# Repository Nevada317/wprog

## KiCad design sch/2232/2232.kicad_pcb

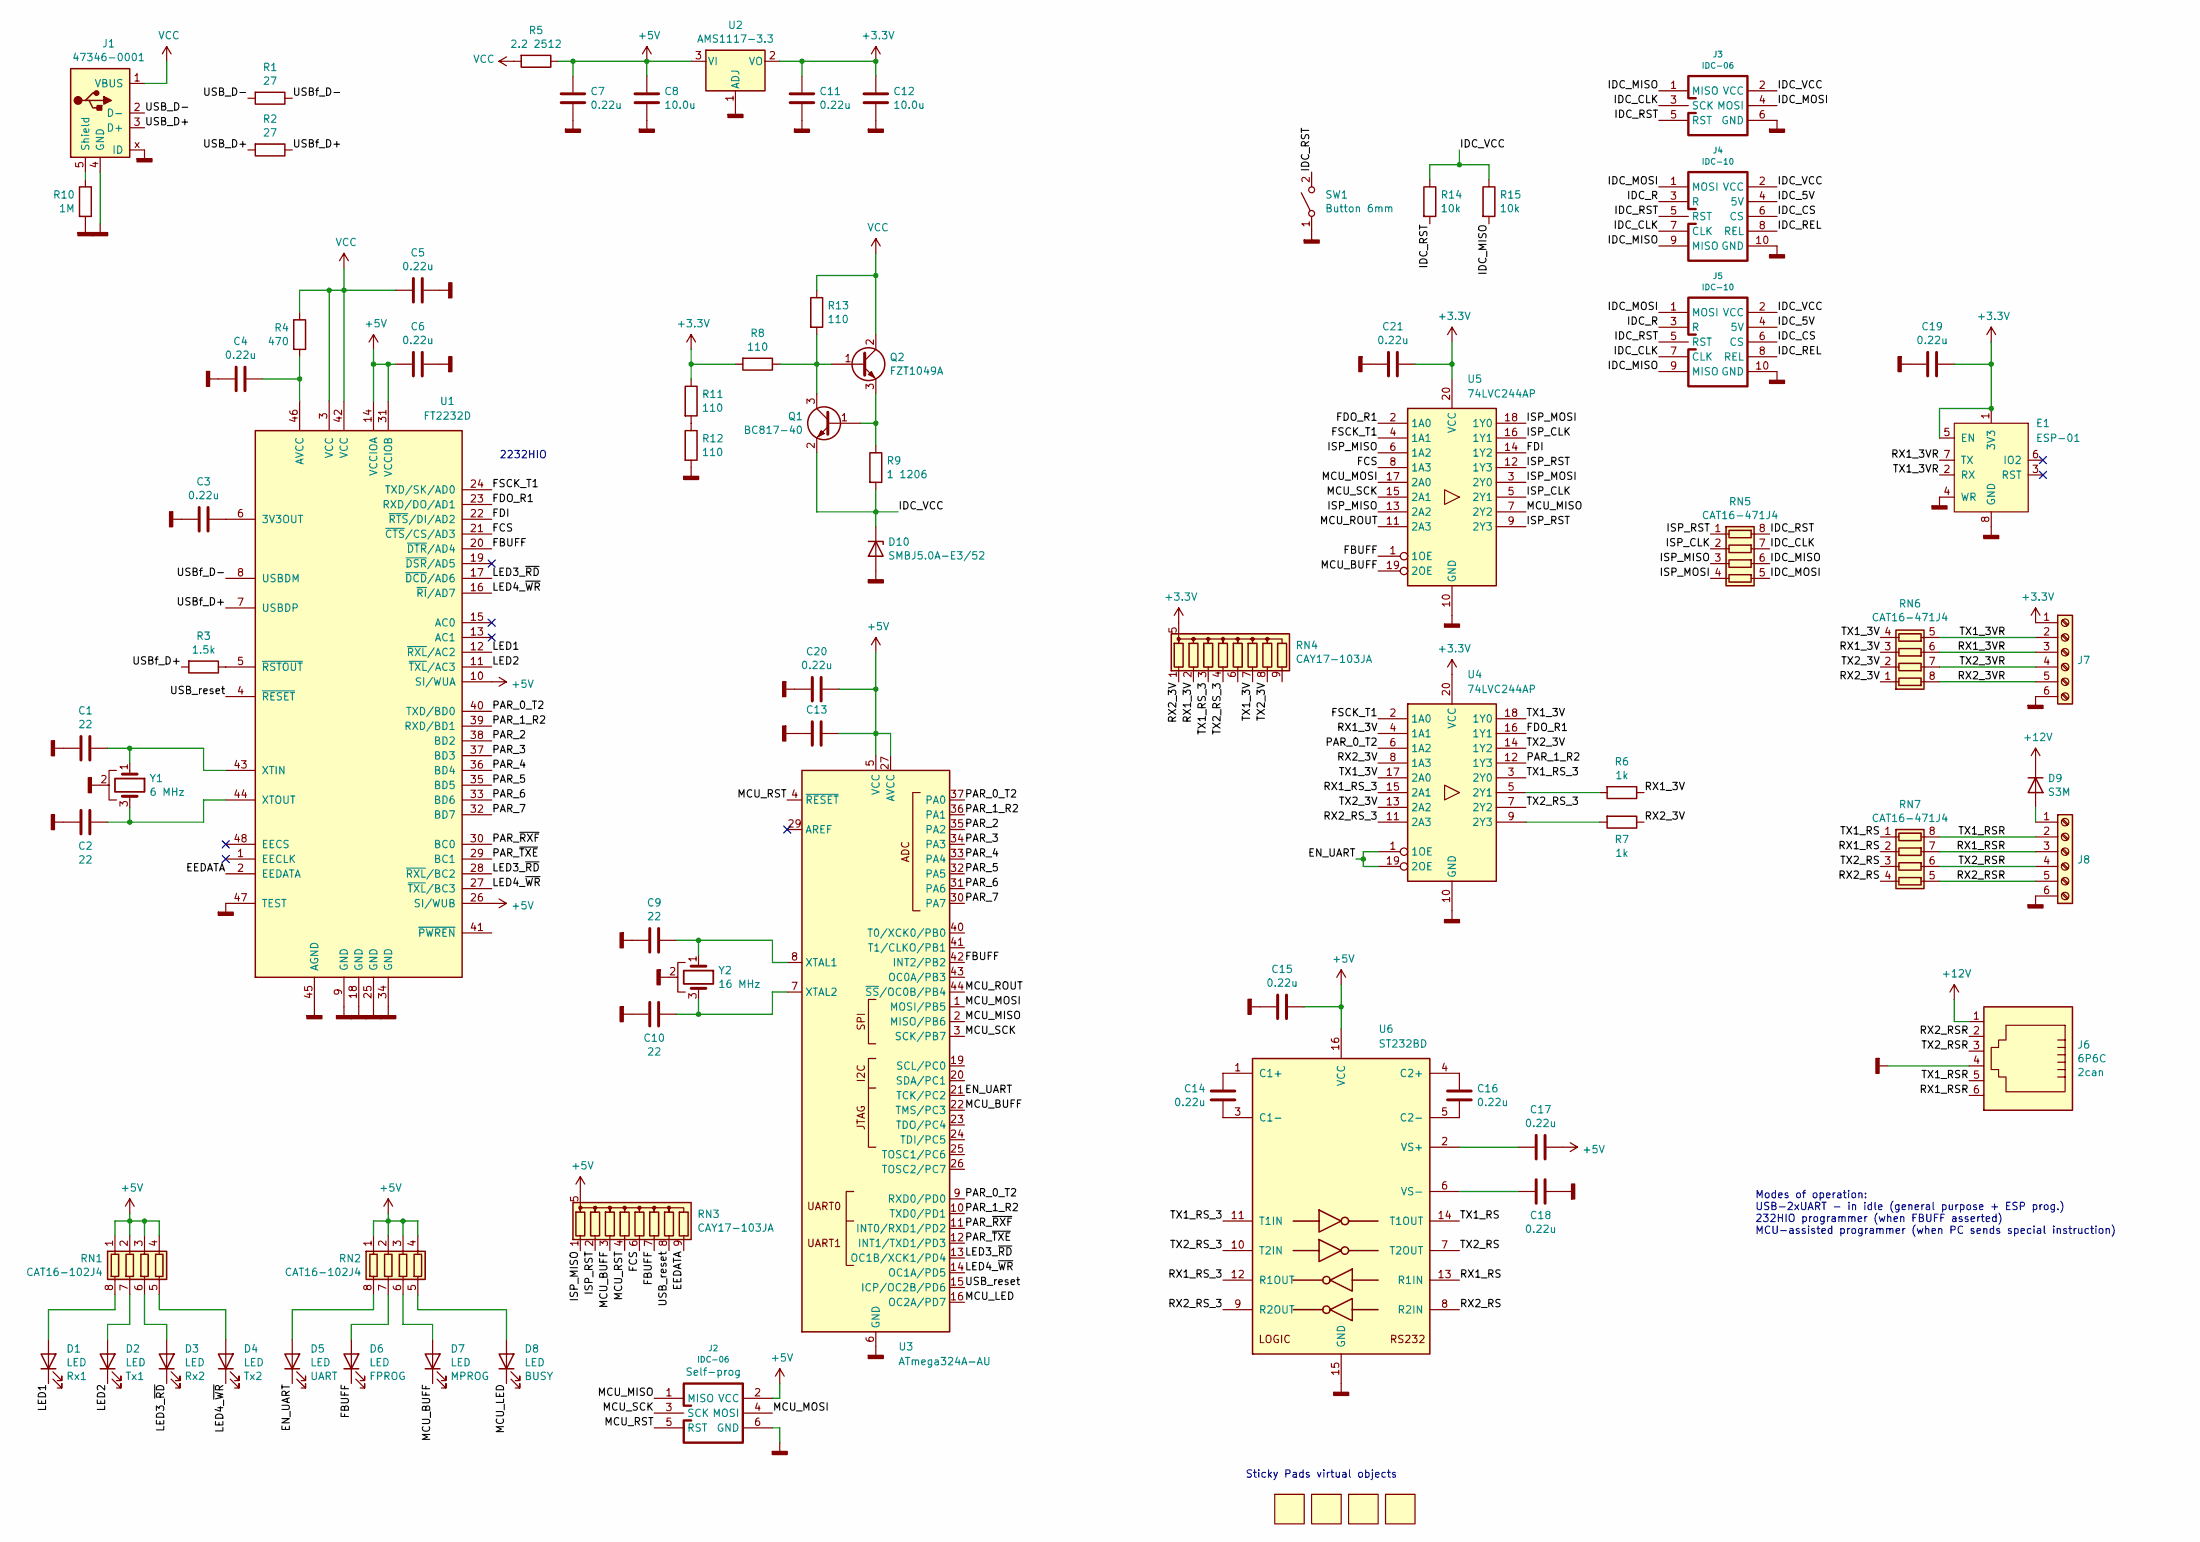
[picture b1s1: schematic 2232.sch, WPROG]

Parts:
C1, C2, C9, C10: 22; C_0603
C3, C4, C5, C6, C7, C11, C13, C14, C15, C16, C17, C18, C19, C20, C21: 0.22u; C_0603
C8, C12: 10.0u; C_1206
D1, D2, D3, D4, D5, D6, D7, D8: LED; LED_KP-2012G
D9: S3M; DO-214AB_SMC
D10: SMBJ5.0A-E3/52; DO-214AA_SMB
E1: ESP-01
J1: 47346-0001; USB_micro_47346
J2: IDC-06; PLD-6
J3: IDC-06; IDC_Header_Straight_6pins
J4, J5: IDC-10; IDC_Header_Straight_10pins
J6: 6P6C; TJ1A-6P6C_new
J7, J8: Screw_Terminal_01x06; Terminal_3.5mm_x6
Q1: BC817-40; SOT-23
Q2: FZT1049A; SOT-223
R1, R2: 27; R_0603
R3: 1.5k; R_0603
R4: 470; R_0603
R5: 2.2 2512; R_2512
R6, R7: 1k; R_0603
R8, R11, R12, R13: 110; R_0603
R9: 1 1206; R_1206
R10: 1M; R_0603
R14, R15: 10k; R_0603
RN1, RN2: CAT16-102J4; R_CAT-16-4
RN3, RN4: CAY17-103JA; R_CAY17
RN5, RN6, RN7: CAT16-471J4; R_CAT-16-4
SW1: Button 6mm; SW_PUSH_6mm
U1: FT2232D; LQFP-48_7x7mm_P0.5mm
U2: AMS1117-3.3; SOT-223
U3: ATmega324A-AU; TQFP-44
U4, U5: 74LVC244AP; TSSOP-20
U6: ST232BD; SOIC-16
V1, V2, V3, V4: Virtual; StickyPad_13mm
Y1: 6 MHz; Crystal_HC-49SMD
Y2: 16 MHz; Crystal_HC-49SMD

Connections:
+3V3: C11.1, C12.1, C19.1, C21.1, E1.1 (3V3), E1.5 (EN), J7.1, R8.2, R11.1, RN4.5 (common), RN4.10 (common), U2.2 (VO), U4.20 (VCC), U5.20 (VCC)
+5V: C6.1, C7.1, C8.1, C13.1, C15.2, C17.1, C20.1, J2.2 (VCC), R5.1, RN1.1 (R1.1), RN1.2 (R2.1), RN1.3 (R3.1), RN1.4 (R4.1), RN2.1 (R1.1), RN2.2 (R2.1), RN2.3 (R3.1), RN2.4 (R4.1), RN3.5 (common), RN3.10 (common), U1.10 (SI/WUA), U1.14 (VCCIOA), U1.26 (SI/WUB), U1.31 (VCCIOB), U2.3 (VI), U3.5 (VCC), U3.17 (VCC), U3.27 (AVCC), U3.38 (VCC), U6.16 (VCC)
+12V: D9.1 (K), J6.1
/EEDATA: RN3.9 (R8), U1.2 (EEDATA)
/EN_UART: D5.1 (K), U3.21 (TCK/PC2), U4.1 (1OE), U4.19 (2OE)
/FBUFF: D6.1 (K), RN3.7 (R6), U1.20 (~DTR~/AD4), U3.42 (INT2/PB2), U5.1 (1OE)
/FCS: RN3.6 (R5), U1.21 (~CTS~/CS/AD3), U5.8 (1A3)
/FDI: U1.22 (~RTS~/DI/AD2), U5.14 (1Y2)
/FDO_R1: U1.23 (RXD/DO/AD1), U4.16 (1Y1), U5.2 (1A0)
/FSCK_T1: U1.24 (TXD/SK/AD0), U4.2 (1A0), U5.4 (1A1)
/IDC_5V: J4.4 (5V), J5.4 (5V)
/IDC_CLK: J3.3 (SCK), J4.7 (CLK), J5.7 (CLK), RN5.7 (R2.2)
/IDC_CS: J4.6 (CS), J5.6 (CS)
/IDC_MISO: J3.1 (MISO), J4.9 (MISO), J5.9 (MISO), R15.2, RN5.6 (R3.2)
/IDC_MOSI: J3.4 (MOSI), J4.1 (MOSI), J5.1 (MOSI), RN5.5 (R4.2)
/IDC_R: J4.3 (R), J5.3 (R)
/IDC_REL: J4.8 (REL), J5.8 (REL)
/IDC_RST: J3.5 (RST), J4.5 (RST), J5.5 (RST), R14.2, RN5.8 (R1.2), SW1.2 (B)
/IDC_VCC: D10.1 (K), J3.2 (VCC), J4.2 (VCC), J5.2 (VCC), Q1.2 (E), R9.2, R14.1, R15.1
/ISP_CLK: RN5.2 (R2.1), U5.5 (2Y1), U5.16 (1Y1)
/ISP_MISO: RN3.1 (R1), RN5.3 (R3.1), U5.6 (1A2), U5.13 (2A2)
/ISP_MOSI: RN5.4 (R4.1), U5.3 (2Y0), U5.18 (1Y0)
/ISP_RST: RN3.2 (R2), RN5.1 (R1.1), U5.9 (2Y3), U5.12 (1Y3)
/LED1: D1.1 (K), U1.12 (~RXL~/AC2)
/LED2: D2.1 (K), U1.11 (~TXL~/AC3)
/LED3_~RD: D3.1 (K), U1.17 (~DCD~/AD6), U1.28 (~RXL~/BC2), U3.13 (OC1B/XCK1/PD4)
/LED4_~WR: D4.1 (K), U1.16 (~RI~/AD7), U1.27 (~TXL~/BC3), U3.14 (OC1A/PD5)
/MCU_BUFF: D7.1 (K), RN3.3 (R3), U3.22 (TMS/PC3), U5.19 (2OE)
/MCU_LED: D8.1 (K), U3.16 (OC2A/PD7)
/MCU_MISO: J2.1 (MISO), U3.2 (MISO/PB6), U5.7 (2Y2)
/MCU_MOSI: J2.4 (MOSI), U3.1 (MOSI/PB5), U5.17 (2A0)
/MCU_ROUT: U3.44 (~SS~/OC0B/PB4), U5.11 (2A3)
/MCU_RST: J2.5 (RST), RN3.4 (R4), U3.4 (~RESET)
/MCU_SCK: J2.3 (SCK), U3.3 (SCK/PB7), U5.15 (2A1)
/PAR_0_T2: U1.40 (TXD/BD0), U3.9 (RXD0/PD0), U3.37 (PA0), U4.6 (1A2)
/PAR_1_R2: U1.39 (RXD/BD1), U3.10 (TXD0/PD1), U3.36 (PA1), U4.12 (1Y3)
/PAR_2: U1.38 (BD2), U3.35 (PA2)
/PAR_3: U1.37 (BD3), U3.34 (PA3)
/PAR_4: U1.36 (BD4), U3.33 (PA4)
/PAR_5: U1.35 (BD5), U3.32 (PA5)
/PAR_6: U1.33 (BD6), U3.31 (PA6)
/PAR_7: U1.32 (BD7), U3.30 (PA7)
/PAR_~RXF: U1.30 (BC0), U3.11 (INT0/RXD1/PD2)
/PAR_~TXE: U1.29 (BC1), U3.12 (INT1/TXD1/PD3)
/RX1_3V: R6.1, RN4.2 (R2), RN6.3 (R3.1), U4.4 (1A1)
/RX1_3VR: E1.7 (TX), J7.3, RN6.6 (R3.2)
/RX1_RS: RN7.2 (R2.1), U6.13 (R1IN)
/RX1_RSR: J6.6, J8.3, RN7.7 (R2.2)
/RX1_RS_3: U4.15 (2A1), U6.12 (R1OUT)
/RX2_3V: R7.1, RN4.1 (R1), RN6.1 (R1.1), U4.8 (1A3)
/RX2_3VR: J7.5, RN6.8 (R1.2)
/RX2_RS: RN7.4 (R4.1), U6.8 (R2IN)
/RX2_RSR: J6.2, J8.5, RN7.5 (R4.2)
/RX2_RS_3: U4.11 (2A3), U6.9 (R2OUT)
/TX1_3V: RN4.7 (R6), RN6.4 (R4.1), U4.17 (2A0), U4.18 (1Y0)
/TX1_3VR: E1.2 (RX), J7.2, RN6.5 (R4.2)
/TX1_RS: RN7.1 (R1.1), U6.14 (T1OUT)
/TX1_RSR: J6.5, J8.2, RN7.8 (R1.2)
/TX1_RS_3: RN4.3 (R3), U4.3 (2Y0), U6.11 (T1IN)
/TX2_3V: RN4.8 (R7), RN6.2 (R2.1), U4.13 (2A2), U4.14 (1Y2)
/TX2_3VR: J7.4, RN6.7 (R2.2)
/TX2_RS: RN7.3 (R3.1), U6.7 (T2OUT)
/TX2_RSR: J6.3, J8.4, RN7.6 (R3.2)
/TX2_RS_3: RN4.4 (R4), U4.7 (2Y2), U6.10 (T2IN)
/USB_D+: J1.3 (D+), R2.2
/USB_D-: J1.2 (D-), R1.2
/USB_reset: RN3.8 (R7), U1.4 (~RESET), U3.15 (ICP/OC2B/PD6)
/USBf_D+: R2.1, R3.2, U1.7 (USBDP)
/USBf_D-: R1.1, U1.8 (USBDM)
GNDD: C1.2, C2.2, C3.2, C4.2, C5.2, C6.2, C7.2, C8.2, C9.2, C10.2, C11.2, C12.2, C13.2, C15.1, C18.1, C19.2, C20.2, C21.2, D10.2 (A), E1.4 (WR), E1.8 (GND), J1.4 (GND), J1.x (ID), J2.6 (GND), J3.6 (GND), J4.10 (GND), J5.10 (GND), J6.4, J7.6, J8.6, R10.2, R12.2, SW1.1 (A), U1.9 (GND), U1.18 (GND), U1.25 (GND), U1.34 (GND), U1.45 (AGND), U1.47 (TEST), U2.1 (ADJ), U3.6 (GND), U3.18 (GND), U3.28 (GND), U3.39 (GND), U4.10 (GND), U5.10 (GND), U6.15 (GND), Y1.2, Y2.2
unnamed: C1.1, U1.43 (XTIN), Y1.1
unnamed: C2.1, U1.44 (XTOUT), Y1.3
unnamed: C3.1, U1.6 (3V3OUT)
unnamed: C4.1, R4.2, U1.46 (AVCC)
unnamed: C9.1, U3.8 (XTAL1), Y2.1
unnamed: C10.1, U3.7 (XTAL2), Y2.3
unnamed: C14.1, U6.1 (C1+)
unnamed: C14.2, U6.3 (C1-)
unnamed: C16.1, U6.4 (C2+)
unnamed: C16.2, U6.5 (C2-)
unnamed: C17.2, U6.2 (VS+)
unnamed: C18.2, U6.6 (VS-)
unnamed: D1.2 (A), RN1.8 (R1.2)
unnamed: D2.2 (A), RN1.7 (R2.2)
unnamed: D3.2 (A), RN1.6 (R3.2)
unnamed: D4.2 (A), RN1.5 (R4.2)
unnamed: D5.2 (A), RN2.8 (R1.2)
unnamed: D6.2 (A), RN2.7 (R2.2)
unnamed: D7.2 (A), RN2.6 (R3.2)
unnamed: D8.2 (A), RN2.5 (R4.2)
unnamed: D9.2 (A), J8.1
unnamed: J1.5 (Shield), R10.1
unnamed: Q1.1 (B), Q2.3 (E), R9.1
unnamed: Q1.3 (C), Q2.1 (B), R8.1, R13.2
unnamed: R3.1, U1.5 (~RSTOUT)
unnamed: R6.2, U4.5 (2Y1)
unnamed: R7.2, U4.9 (2Y3)
unnamed: R11.2, R12.1
VCC: C5.1, J1.1 (VBUS), Q2.2 (C), R4.1, R5.2, R13.1, U1.3 (VCC), U1.42 (VCC)

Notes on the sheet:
2232HIO
Modes of operation: USB-2xUART - in idle (general purpose + ESP prog.) 232HIO programmer (when FBUFF asserted) MCU-assisted programmer (when PC sends special instruction)
Sticky Pads virtual objects

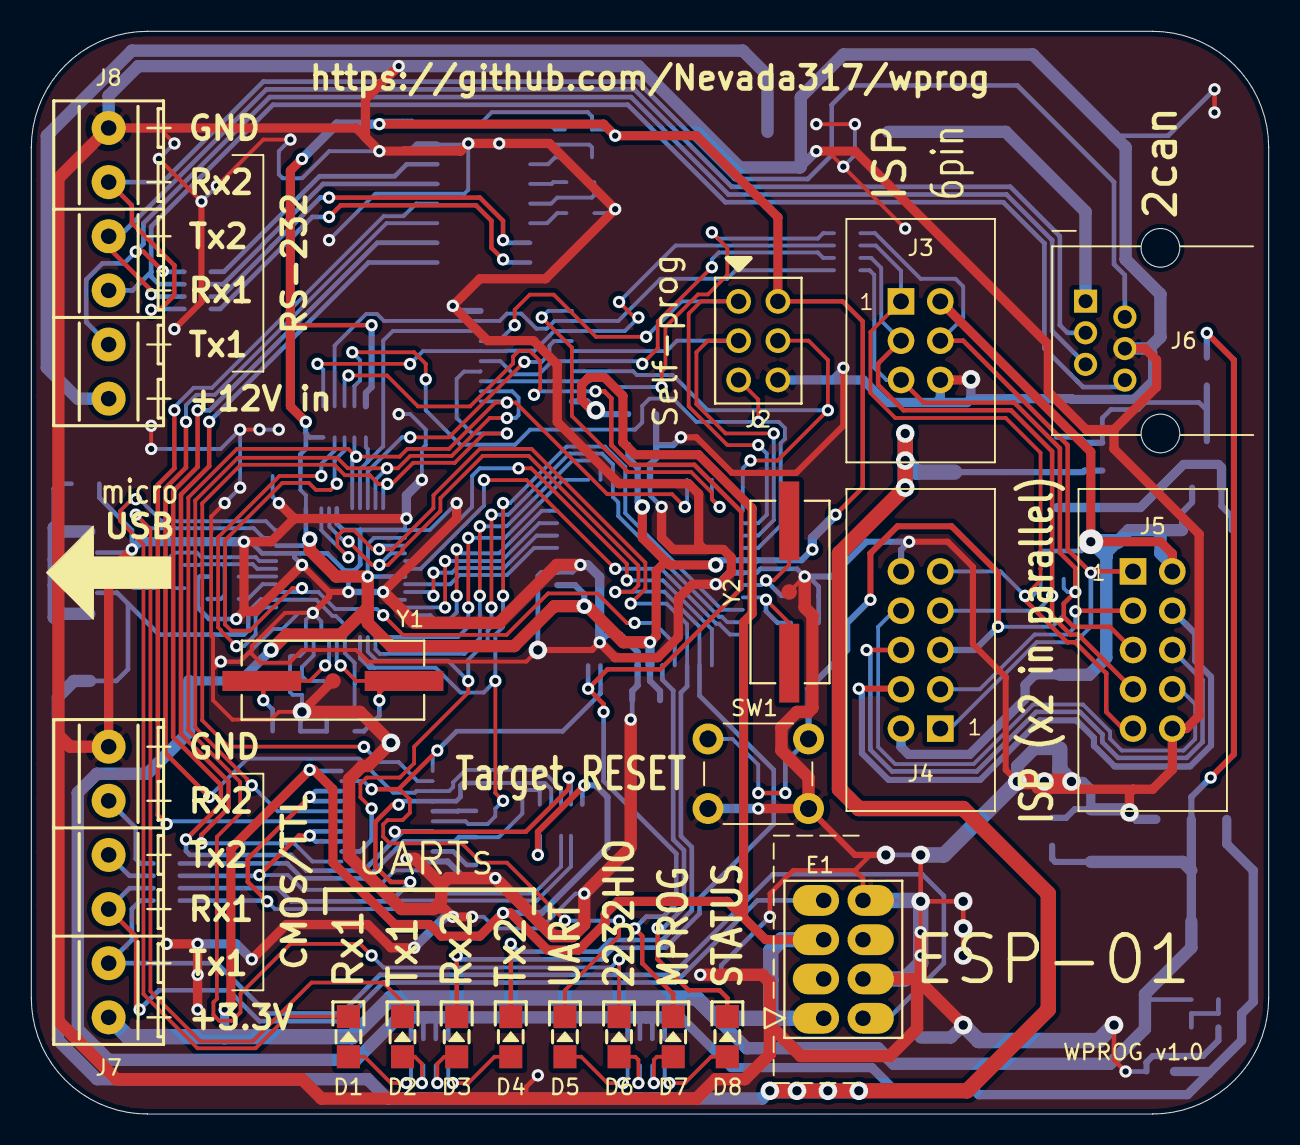
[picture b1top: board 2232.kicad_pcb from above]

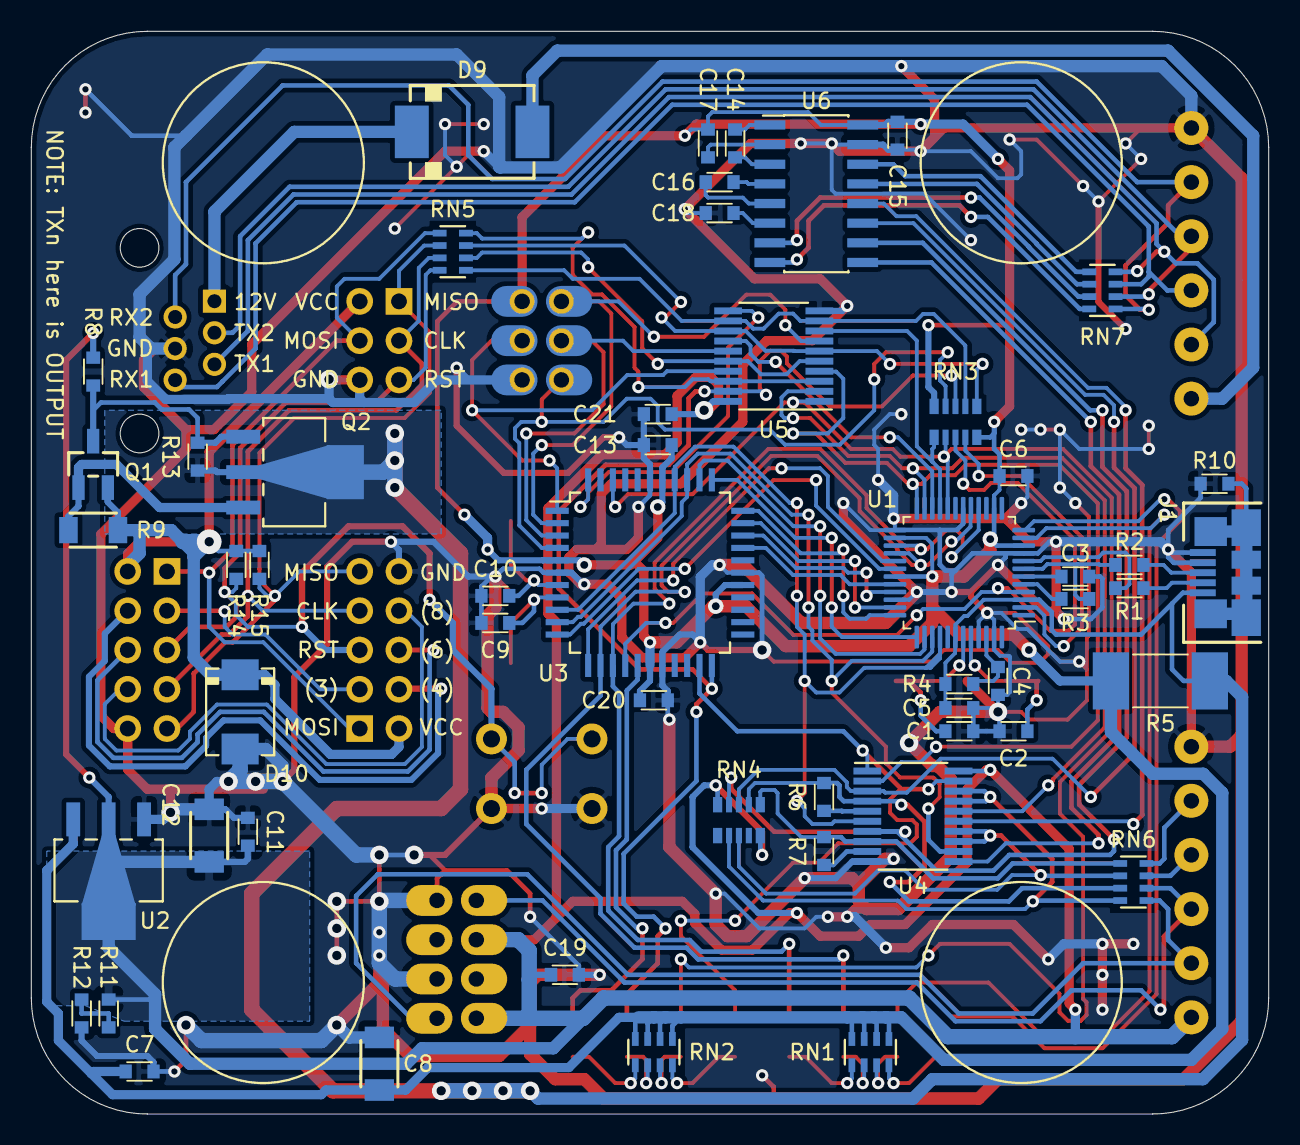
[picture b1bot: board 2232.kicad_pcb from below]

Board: 2 copper layers, 80.0 x 70.0 mm, 77 parts (58 on the bottom side), 99 nets.

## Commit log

2020-11-21 Some thoughts
2020-12-11 Schematic stub
2020-12-12 Strobes added
2020-12-12 HC138 added
2020-12-12 Names fixed. Footprints assigned
2020-12-12 Annotated. PCB exported
2020-12-12 PCB orientation stub
2020-12-12 UART multiplexing
2020-12-13 Routing started
2020-12-14 UARTs routed trough connectors
2020-12-14 All components on-board
2020-12-14 RN remap
2020-12-14 Sides separated
2020-12-14 ISP routed
2020-12-14 All footprinted elements are routed
2020-12-15 VCC routed
2020-12-15 IDC rotated
2020-12-15 Zones added
2020-12-16 Cleanup
2020-12-16 No-fill zones
2020-12-16 Minor updates
2020-12-19 pcb updates. Looks ready
2020-12-19 PCB silk added
2020-12-19 Gerbers exported
2020-12-19 STEP models update
2020-12-20 Pullups to RST and MISO added
2020-12-20 Silk updates
2020-12-20 Reset button added
2020-12-20 zipped
2020-12-20 Step update
2020-12-20 Remove duplicate PDF
2020-12-26 Include stub added
2020-12-26 Loop added
2020-12-26 Macro file added
2020-12-26 Memclear added
2020-12-26 Pin init
2020-12-26 Mode selector created
2021-01-05 UART Rx stub added
2021-01-05 PC C stub added
2021-01-05 Option parser added
2021-01-05 Add variable to store input string (port)
2021-01-05 Task.c/h added and looks like working
2021-01-05 Pages linked list implemented
2021-01-05 Pages called
2021-01-05 Tasks structure changed
2021-01-05 Intel hex parser added
2021-01-06 Data from ihex is now separated by pages
2021-01-06 tty.c inserted
2021-01-06 UART looks like working
2021-01-07 Transport constructor/destructor added
2021-01-07 Subscribers added
2021-01-07 Transport parcel - raw parcel generated and printed
2021-01-07 Byte stuffing added
2021-01-07 Data sent to real port
2021-01-07 Reader in separate thread added
2021-01-07 Data should be stored now
2021-01-07 Reader looks like working
2021-01-07 CRC added
2021-01-07 Removet bunch of useless printf's
2021-01-08 Specs update
2021-01-08 Protocol constants defined as pc/src/protocol.h
2021-01-11 Remove nasty warning in test case
2022-02-01 Update Makefile
2022-02-01 Debug calls added
2022-02-01 Init ONE register
2022-02-01 Modified echo added to 1w module
2022-02-01 Bit operations implemented
2022-02-01 Fix reset
2022-02-01 Read rom works
2023-05-05 Add m164p support
2023-05-05 ISR table separation
2023-05-05 Remove gefault MEGA and fix dependencies in Makefile
